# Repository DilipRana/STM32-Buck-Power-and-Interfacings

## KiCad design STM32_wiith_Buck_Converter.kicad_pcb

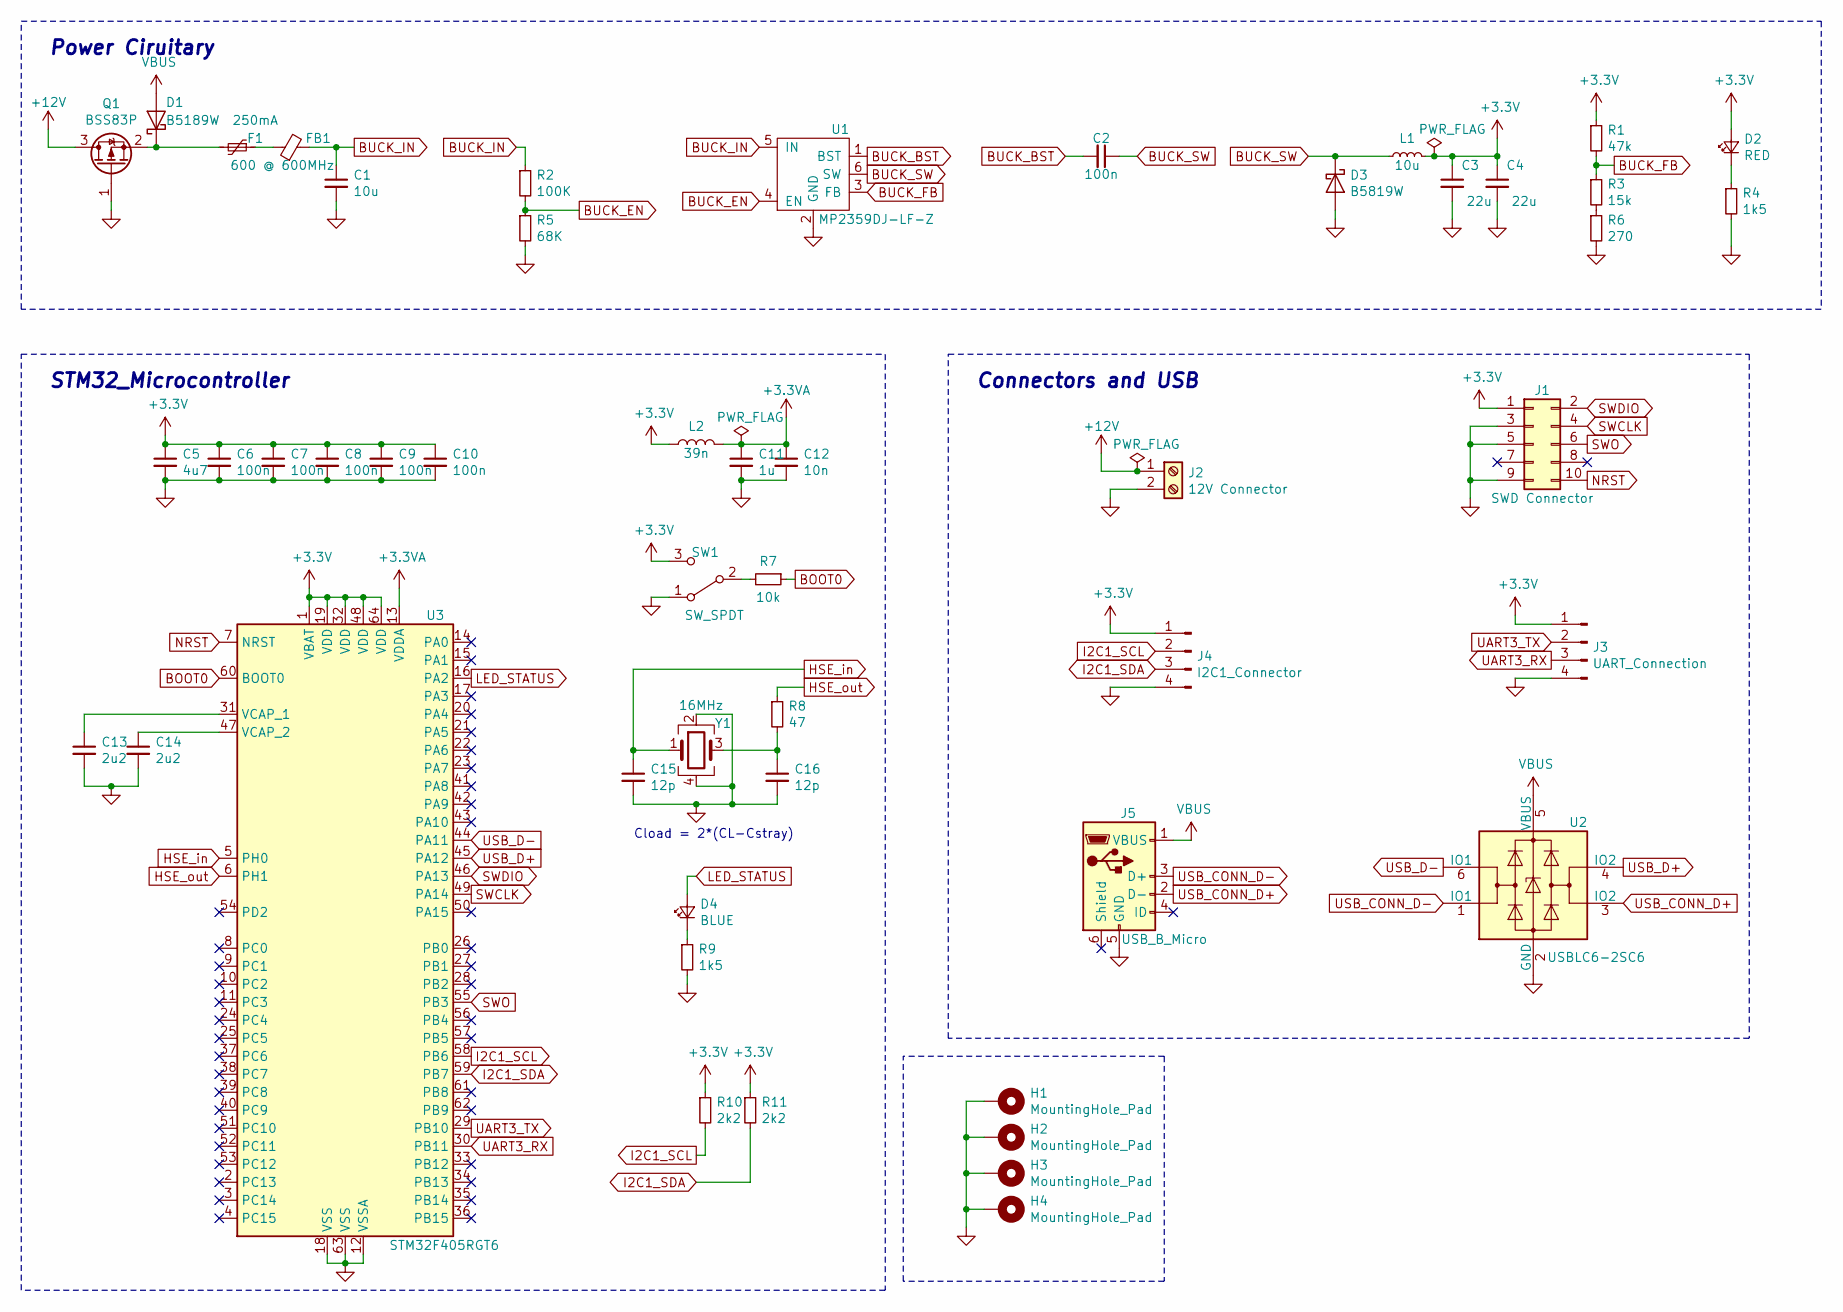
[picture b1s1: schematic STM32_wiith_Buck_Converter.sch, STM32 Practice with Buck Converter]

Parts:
C1: 10u; C_0603_1608Metric
C2: 100n; C_0603_1608Metric
C3, C4: 22u; C_1206_3216Metric
C5: 4u7; C_1206_3216Metric
C6, C7, C8, C9, C10: 100n; C_0402_1005Metric
C11: 1u; C_0603_1608Metric
C12: 10n; C_0402_1005Metric
C13, C14: 2u2; C_0402_1005Metric
C15, C16: 12p; C_0402_1005Metric
D1: B5189W; D_SOD-123
D2: RED; LED_0603_1608Metric
D3: B5819W; D_SOD-123
D4: BLUE; LED_0603_1608Metric
F1: 250mA; Fuse_1206_3216Metric
FB1: 600 @ 600MHz; L_0805_2012Metric
H1, H2: MountingHole_Pad; MountingHole_4.3mm_M4_Pad_Via
H3, H4: MountingHole_Pad; MountingHole_4.5mm_Pad_Via
J1: SWD Connector; PinHeader_2x05_P1.00mm_Vertical_SMD
J2: 12V Connector; TerminalBlock_4Ucon_1x02_P3.50mm_Horizontal
J3: UART_Connection; Molex_PicoBlade_53048-0810_1x04_P1.25mm_Horizontal
J4: I2C1_Connector; Molex_PicoBlade_53048-0810_1x04_P1.25mm_Horizontal
J5: USB_B_Micro; USB_Micro-B_Wuerth_629105150521
L1: 10u; L_0805_2012Metric
L2: 39n; L_0402_1005Metric
Q1: BSS83P; SOT-23
R1: 47k; R_0402_1005Metric
R2: 100K; R_0201_0603Metric
R3: 15k; R_0402_1005Metric
R4, R9: 1k5; R_0603_1608Metric
R5: 68K; R_0201_0603Metric
R6: 270; R_0402_1005Metric
R7: 10k; R_0402_1005Metric
R8: 47; R_0402_1005Metric
R10, R11: 2k2; R_0402_1005Metric
SW1: SW_SPDT; SW_SPDT_PCM12
U1: MP2359DJ-LF-Z; SOT-23-6
U2: USBLC6-2SC6; SOT-23-6
U3: STM32F405RGT6; LQFP-64_10x10mm_P0.5mm
Y1: 16MHz; Crystal_SMD_3225-4Pin_3.2x2.5mm

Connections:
+3.3VA: C11.1, C12.1, L2.2, U3.13 (VDDA)
+3V3: C3.1, C4.1, C5.1, C6.1, C7.1, C8.1, C9.1, C10.1, D2.2 (A), J1.1, J3.1, J4.1, L1.2, L2.1, R1.1, R10.1, R11.1, SW1.3 (C), U3.1 (VBAT), U3.19 (VDD), U3.32 (VDD), U3.48 (VDD), U3.64 (VDD)
+12V: J2.1, Q1.3 (D)
BOOT0: R7.1, U3.60 (BOOT0)
BUCK_BST: C2.2, U1.1 (BST)
BUCK_EN: R2.2, R5.1, U1.4 (EN)
BUCK_FB: R1.2, R3.1, U1.3 (FB)
BUCK_IN: C1.1, FB1.2, R2.1, U1.5 (IN)
BUCK_SW: C2.1, D3.1 (K), L1.1, U1.6 (SW)
GND: C1.2, C3.2, C4.2, C5.2, C6.2, C7.2, C8.2, C9.2, C10.2, C11.2, C12.2, C13.2, C14.2, C15.2, C16.2, D3.2 (A), H1.1, H2.1, H3.1, H4.1, J1.3, J1.5, J1.9, J2.2, J3.4, J4.4, J5.5 (GND), Q1.1 (G), R4.2, R5.2, R6.2, R9.2, SW1.1 (A), U1.2 (GND), U2.2 (GND), U3.12 (VSSA), U3.18 (VSS), U3.63 (VSS), Y1.2, Y1.4
HSE_in: C15.1, U3.5 (PH0), Y1.1
HSE_out: R8.1, U3.6 (PH1)
I2C1_SCL: J4.2, R10.2, U3.58 (PB6)
I2C1_SDA: J4.3, R11.2, U3.59 (PB7)
LED_STATUS: D4.2 (A), U3.16 (PA2)
NRST: J1.10, U3.7 (NRST)
unnamed: C13.1, U3.31 (VCAP_1)
unnamed: C14.1, U3.47 (VCAP_2)
unnamed: C16.1, R8.2, Y1.3
unnamed: D1.1 (K), F1.2, Q1.2 (S)
unnamed: D2.1 (K), R4.1
unnamed: D4.1 (K), R9.1
unnamed: F1.1, FB1.1
unnamed: R3.2, R6.1
unnamed: R7.2, SW1.2 (B)
SWCLK: J1.4, U3.49 (PA14)
SWDIO: J1.2, U3.46 (PA13)
SWO: J1.6, U3.55 (PB3)
UART3_RX: J3.3, U3.30 (PB11)
UART3_TX: J3.2, U3.29 (PB10)
USB_CONN_D+: J5.2 (D-), U2.3 (IO2)
USB_CONN_D-: J5.3 (D+), U2.1 (IO1)
USB_D+: U2.4 (IO2), U3.45 (PA12)
USB_D-: U2.6 (IO1), U3.44 (PA11)
VBUS: D1.2 (A), J5.1 (VBUS), U2.5 (VBUS)

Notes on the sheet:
STM32_Microcontroller
Cload = 2*(CL-Cstray)
Power Ciruitary
Connectors and USB

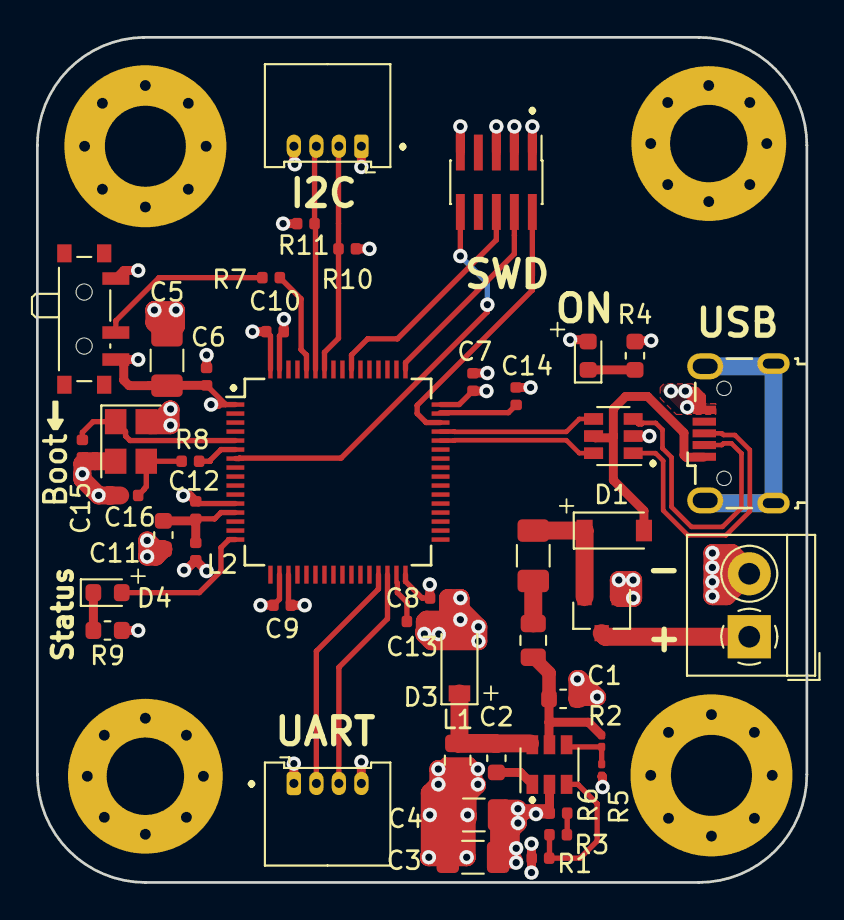
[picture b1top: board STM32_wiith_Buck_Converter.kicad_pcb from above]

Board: 4 copper layers, 42.8 x 47.0 mm, 50 parts (0 on the bottom side), 35 nets.

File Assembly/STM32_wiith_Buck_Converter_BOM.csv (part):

"Source:","D:\Workspace\Kicad\STM32_wiith_Buck_Converter\STM32_wiith_Buck_Converter.sch"
"Date:","04-Sep-22 8:22:11 PM"
"Tool:","Eeschema (5.0.1)-4"
"Generator:","C:\Program Files\KiCad\bin\scripting\plugins/bom_csv_grouped_by_value.py"
"Component Count:","50"

"Individual Components:"

"Item","Qty","Reference(s)","Value","LibPart","Footprint","Datasheet"
"","","C1","10u","Device:C_Small","Capacitor_SMD:C_0603_1608Metric","~"
"","","C2","100n","Device:C_Small","Capacitor_SMD:C_0603_1608Metric","~"
"","","C3","22u","Device:C_Small","Capacitor_SMD:C_1206_3216Metric","~"
"","","C4","22u","Device:C_Small","Capacitor_SMD:C_1206_3216Metric","~"
"","","C5","4u7","Device:C_Small","Capacitor_SMD:C_1206_3216Metric","~"
"","","C6","100n","Device:C_Small","Capacitor_SMD:C_0402_1005Metric","~"
"","","C7","100n","Device:C_Small","Capacitor_SMD:C_0402_1005Metric","~"
"","","C8","100n","Device:C_Small","Capacitor_SMD:C_0402_1005Metric","~"
"","","C9","100n","Device:C_Small","Capacitor_SMD:C_0402_1005Metric","~"
"","","C10","100n","Device:C_Small","Capacitor_SMD:C_0402_1005Metric","~"
"","","C11","1u","Device:C_Small","Capacitor_SMD:C_0603_1608Metric","~"
"","","C12","10n","Device:C_Small","Capacitor_SMD:C_0402_1005Metric","~"
"","","C13","2u2","Device:C_Small","Capacitor_SMD:C_0402_1005Metric","~"
"","","C14","2u2","Device:C_Small","Capacitor_SMD:C_0402_1005Metric","~"
"","","C15","12p","Device:C_Small","Capacitor_SMD:C_0402_1005Metric","~"
"","","C16","12p","Device:C_Small","Capacitor_SMD:C_0402_1005Metric","~"
"","","D1","B5189W","Device:D_Schottky","Diode_SMD:D_SOD-123","~"
"","","D2","RED","Device:LED_Small","LED_SMD:LED_0603_1608Metric","~"
"","","D3","B5819W","Device:D_Schottky","Diode_SMD:D_SOD-123","~"
"","","D4","BLUE","Device:LED_Small","LED_SMD:LED_0603_1608Metric","~"
"","","F1","250mA","Device:Polyfuse_Small","Fuse:Fuse_1206_3216Metric","~"
"","","FB1","600 @ 600MHz","Device:Ferrite_Bead_Small","Inductor_SMD:L_0805_2012Metric","~"
"","","H1","MountingHole_Pad","Mechanical:MountingHole_Pad","MountingHole:MountingHole_4.3mm_M4_Pad_Via","~"
"","","H2","MountingHole_Pad","Mechanical:MountingHole_Pad","MountingHole:MountingHole_4.3mm_M4_Pad_Via","~"
"","","H3","MountingHole_Pad","Mechanical:MountingHole_Pad","MountingHole:MountingHole_4.5mm_Pad_Via","~"
"","","H4","MountingHole_Pad","Mechanical:MountingHole_Pad","MountingHole:MountingHole_4.5mm_Pad_Via","~"
"","","J1","SWD Connector","Connector_Generic:Conn_02x05_Odd_Even","Connector_PinHeader_1.00mm:PinHeader_2x05_P1.00mm_Vertical_SMD","~"
"","","J2","12V Connector","Connector:Screw_Terminal_01x02","TerminalBlock_4Ucon:TerminalBlock_4Ucon_1x02_P3.50mm_Horizontal","~"
"","","J3","UART_Connection","Connector:Conn_01x04_Male","Connector_Molex:Molex_PicoBlade_53048-0810_1x04_P1.25mm_Horizontal","~"
"","","J4","I2C1_Connector","Connector:Conn_01x04_Male","Connector_Molex:Molex_PicoBlade_53048-0810_1x04_P1.25mm_Horizontal","~"
"","","J5","USB_B_Micro","Connector:USB_B_Micro","Connector_USB:USB_Micro-B_Wuerth_629105150521","~"
"","","L1","10u","Device:L_Small","Inductor_SMD:L_0805_2012Metric","~"
"","","L2","39n","Device:L","Inductor_SMD:L_0402_1005Metric","~"
"","","Q1","BSS83P","Transistor_FET:BSS83P","Package_TO_SOT_SMD:SOT-23","http://www.farnell.com/datasheets/1835997.pdf"
"","","R1","47k","Device:R_Small","Resistor_SMD:R_0402_1005Metric","~"
"","","R2","100K","Device:R_Small","Resistor_SMD:R_0201_0603Metric","~"
"","","R3","15k","Device:R_Small","Resistor_SMD:R_0402_1005Metric","~"
"","","R4","1k5","Device:R_Small","Resistor_SMD:R_0603_1608Metric","~"
"","","R5","68K","Device:R_Small","Resistor_SMD:R_0201_0603Metric","~"
"","","R6","270","Device:R_Small","Resistor_SMD:R_0402_1005Metric","~"
"","","R7","10k","Device:R_Small","Resistor_SMD:R_0402_1005Metric","~"
"","","R8","47","Device:R_Small","Resistor_SMD:R_0402_1005Metric","~"
"","","R9","1k5","Device:R_Small","Resistor_SMD:R_0603_1608Metric","~"
"","","R10","2k2","Device:R_Small","Resistor_SMD:R_0402_1005Metric","~"
"","","R11","2k2","Device:R_Small","Resistor_SMD:R_0402_1005Metric","~"
"","","SW1","SW_SPDT","Switch:SW_SPDT","Button_Switch_SMD:SW_SPDT_PCM12",""
"","","U1","MP2359DJ-LF-Z","ConvertersICs:MP2359DJ-LF-Z","Package_TO_SOT_SMD:SOT-23-6",""
"","","U2","USBLC6-2SC6","Power_Protection:USBLC6-2SC6","Package_TO_SOT_SMD:SOT-23-6","http://www2.st.com/resource/en/datasheet/CD00050750.pdf"
"","","U3","STM32F405RGT6","MCU_ST_STM32F4:STM32F405RGTx","Package_QFP:LQFP-64_10x10mm_P0.5mm","http://www.st.com/st-web-ui/static/active/en/resource/techni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"
"","","Y1","16MHz","Device:Crystal_GND24","Crystal:Crystal_SMD_3225-4Pin_3.2x2.5mm","~"



"Collated Components:"

"Item","Qty","Reference(s)","Value","LibPart","Footprint","Datasheet"
"1","1","C1","10u","Device:C_Small","Capacitor_SMD:C_0603_1608Metric","~"
"2","1","C2","100n","Device:C_Small","Capacitor_SMD:C_0603_1608Metric","~"
"3","2","C3, C4","22u","Device:C_Small","Capacitor_SMD:C_1206_3216Metric","~"
"4","1","C5","4u7","Device:C_Small","Capacitor_SMD:C_1206_3216Metric","~"
"5","5","C6, C7, C8, C9, C10","100n","Device:C_Small","Capacitor_SMD:C_0402_1005Metric","~"
"6","1","C11","1u","Device:C_Small","Capacitor_SMD:C_0603_1608Metric","~"
"7","1","C12","10n","Device:C_Small","Capacitor_SMD:C_0402_1005Metric","~"
"8","2","C13, C14","2u2","Device:C_Small","Capacitor_SMD:C_0402_1005Metric","~"
"9","2","C15, C16","12p","Device:C_Small","Capacitor_SMD:C_0402_1005Metric","~"
"10","1","D1","B5189W","Device:D_Schottky","Diode_SMD:D_SOD-123","~"
"11","1","D2","RED","Device:LED_Small","LED_SMD:LED_0603_1608Metric","~"
"12","1","D3","B5819W","Device:D_Schottky","Diode_SMD:D_SOD-123","~"
"13","1","D4","BLUE","Device:LED_Small","LED_SMD:LED_0603_1608Metric","~"
"14","1","F1","250mA","Device:Polyfuse_Small","Fuse:Fuse_1206_3216Metric","~"
"15","1","FB1","600 @ 600MHz","Device:Ferrite_Bead_Small","Inductor_SMD:L_0805_2012Metric","~"
"16","2","H1, H2","MountingHole_Pad","Mechanical:MountingHole_Pad","MountingHole:MountingHole_4.3mm_M4_Pad_Via","~"
"17","2","H3, H4","MountingHole_Pad","Mechanical:MountingHole_Pad","MountingHole:MountingHole_4.5mm_Pad_Via","~"
"18","1","J1","SWD Connector","Connector_Generic:Conn_02x05_Odd_Even","Connector_PinHeader_1.00mm:PinHeader_2x05_P1.00mm_Vertical_SMD","~"
"19","1","J2","12V Connector","Connector:Screw_Terminal_01x02","TerminalBlock_4Ucon:TerminalBlock_4Ucon_1x02_P3.50mm_Horizontal","~"
"20","1","J3","UART_Connection","Connector:Conn_01x04_Male","Connector_Molex:Molex_PicoBlade_53048-0810_1x04_P1.25mm_Horizontal","~"
"21","1","J4","I2C1_Connector","Connector:Conn_01x04_Male","Connector_Molex:Molex_PicoBlade_53048-0810_1x04_P1.25mm_Horizontal","~"
"22","1","J5","USB_B_Micro","Connector:USB_B_Micro","Connector_USB:USB_Micro-B_Wuerth_629105150521","~"
"23","1","L1","10u","Device:L_Small","Inductor_SMD:L_0805_2012Metric","~"
"24","1","L2","39n","Device:L","Inductor_SMD:L_0402_1005Metric","~"
"25","1","Q1","BSS83P","Transistor_FET:BSS83P","Package_TO_SOT_SMD:SOT-23","http://www.farnell.com/datasheets/1835997.pdf"
"26","1","R1","47k","Device:R_Small","Resistor_SMD:R_0402_1005Metric","~"
"27","1","R2","100K","Device:R_Small","Resistor_SMD:R_0201_0603Metric","~"
"28","1","R3","15k","Device:R_Small","Resistor_SMD:R_0402_1005Metric","~"
"29","2","R4, R9","1k5","Device:R_Small","Resistor_SMD:R_0603_1608Metric","~"
"30","1","R5","68K","Device:R_Small","Resistor_SMD:R_0201_0603Metric","~"
"31","1","R6","270","Device:R_Small","Resistor_SMD:R_0402_1005Metric","~"
"32","1","R7","10k","Device:R_Small","Resistor_SMD:R_0402_1005Metric","~"
"33","1","R8","47","Device:R_Small","Resistor_SMD:R_0402_1005Metric","~"
"34","2","R10, R11","2k2","Device:R_Small","Resistor_SMD:R_0402_1005Metric","~"
"35","1","SW1","SW_SPDT","Switch:SW_SPDT","Button_Switch_SMD:SW_SPDT_PCM12",""
"36","1","U1","MP2359DJ-LF-Z","ConvertersICs:MP2359DJ-LF-Z","Package_TO_SOT_SMD:SOT-23-6",""
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
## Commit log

2023-05-27 Design Completion
